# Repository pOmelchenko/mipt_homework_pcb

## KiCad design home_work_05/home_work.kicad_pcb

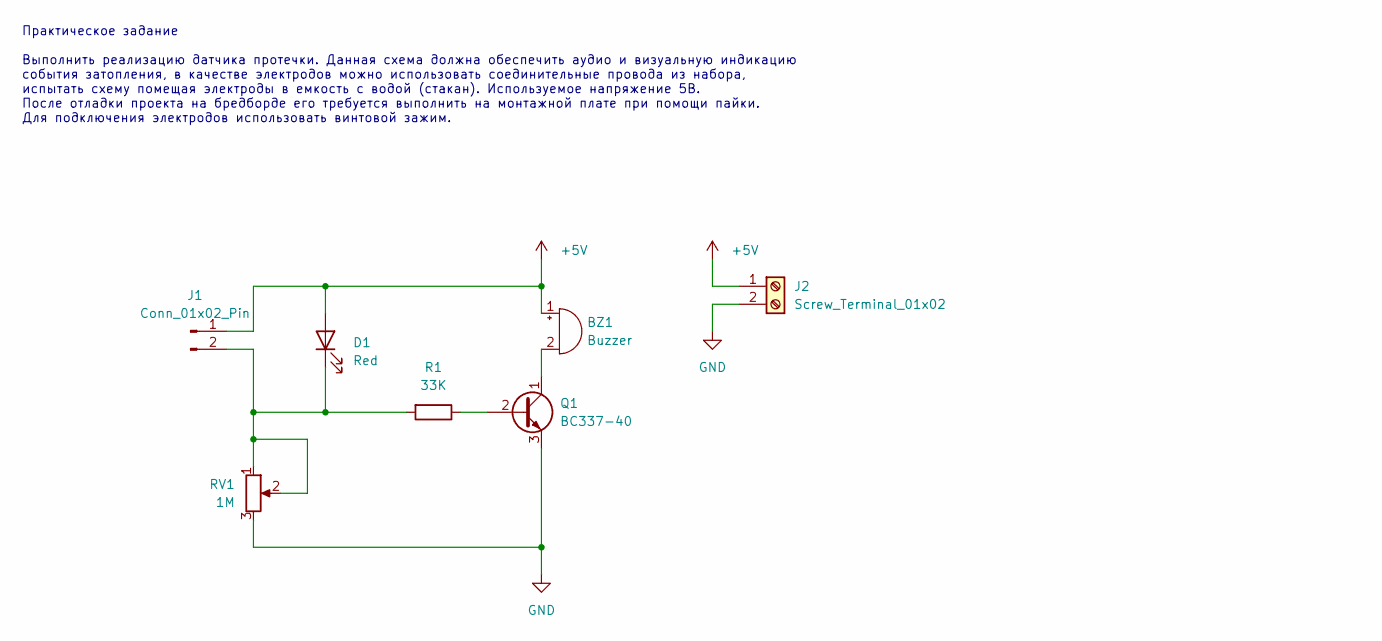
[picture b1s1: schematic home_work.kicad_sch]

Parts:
BZ1: Buzzer; Buzzer_15x7.5RM7.6
D1: Red; LED_D5.0mm
J1: Conn_01x02_Pin; JST_PH_B2B-PH-K_1x02_P2.00mm_Vertical
J2: Screw_Terminal_01x02; FK301-5.0
Q1: BC337-40; TO-92_Inline
R1: 33K; R_Axial_DIN0207_L6.3mm_D2.5mm_P10.16mm_Horizontal
RV1: 1M; Potentiometer_Bourns_3266Y_Vertical

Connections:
+5V: BZ1.1 (+), D1.2 (A), J1.1, J2.1
GND: J2.2, Q1.3 (E), RV1.3
unnamed: BZ1.2 (-), Q1.1 (C)
unnamed: D1.1 (K), J1.2, R1.2, RV1.1, RV1.2
unnamed: Q1.2 (B), R1.1

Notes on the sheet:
Практическое задание Выполнить реализацию датчика протечки. Данная схема должна обеспечить аудио и визуальную индикацию события затопления, в качестве электродов можно использовать соединительные провода из набора, испытать схему помещая электроды в емкость с водой (стакан). Используемое напряжение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

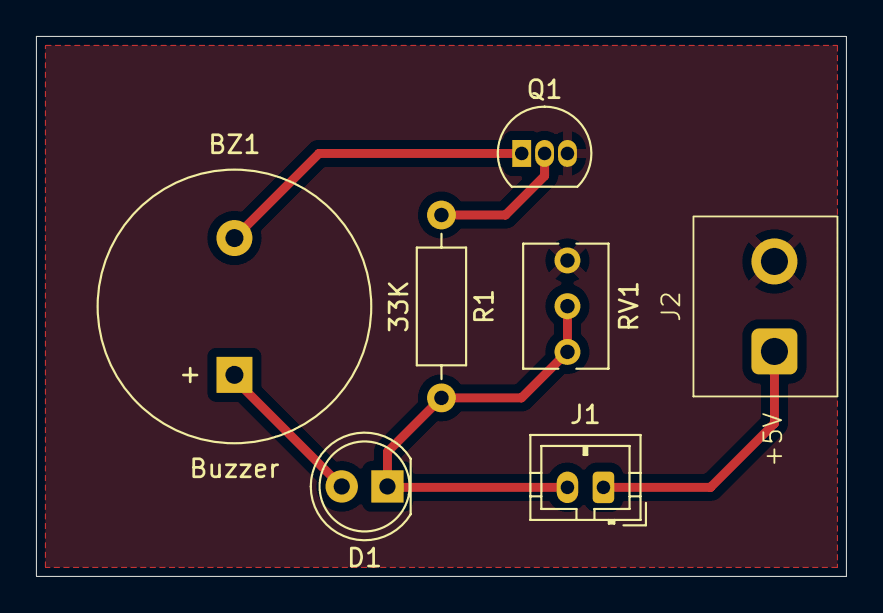
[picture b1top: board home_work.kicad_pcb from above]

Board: 2 copper layers, 45.0 x 30.0 mm, 7 parts (0 on the bottom side), 5 nets.

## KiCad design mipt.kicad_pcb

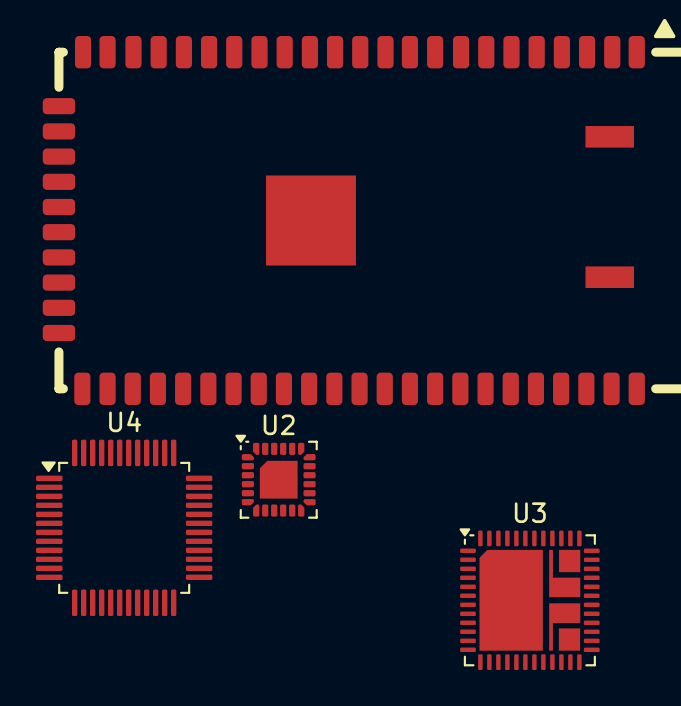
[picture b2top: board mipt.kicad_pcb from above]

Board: 2 copper layers, 4 parts (0 on the bottom side), 4 nets, no tracks yet.

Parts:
U1: HLK-7628N
U2: AW9523B; TQFN-24-1EP_4x4mm_P0.5mm_EP2.1x2.1mm
U3: XS2184; QFN-48-1EP_7x7mm_P0.5mm_EP5.6x5.6mm_1
U4: BL0910; LQFP-48_7x7mm_P0.5mm

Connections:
unnamed: U3.36 (DRAIN1), U3.39 (DRAIN1)
unnamed: U3.29 (DRAIN3), U3.30 (DRAIN3)
unnamed: U3.25 (DRAIN4), U3.26 (DRAIN4)
unnamed: U3.1 (N.C.), U3.15 (N.C.), U3.16 (N.C.), U3.17 (N.C.), U3.19 (N.C.), U3.20 (N.C.), U3.24 (N.C.), U3.38 (N.C.), U3.42 (N.C.), U3.43 (N.C.), U3.44 (N.C.), U3.46 (N.C.)

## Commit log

2024-06-28 init project
2024-07-03 started to do homework 2
2024-07-16 rename symbols library
2024-07-16 add english datasheet
2024-07-16 update symbol of AW9523B
2024-07-16 update basic schema
2024-07-16 add footprint for AW9523B
2024-07-16 update schemas
2024-07-17 update symbol
2024-07-17 add new symbols
2024-07-17 update symbols
2024-07-17 add fp table
2024-07-22 update HLK-7628N
2024-07-23 started to draw footprint for HLK-7628N
2024-07-23 update fp
2024-07-24 update BL0910
2024-07-24 some fixes
2024-07-27 updaye fp QFN-48-1EP
2024-07-28 fix some errors
2024-07-28 cleanup and reorganisation of project
2024-07-28 update schemas structure
2024-07-30 start home work 3. task 1
2024-07-30 fix led labesl to red
2024-08-03 home work 3
2024-08-05 home works 3 and 4
2024-08-06 fix schema for hw 4.1
2024-08-08 update path to hidden folder
2024-08-08 rename folder to hidden
2024-08-11 update hw2
2024-08-11 add datasheets
2024-08-11 update hw3
2024-08-11 add hw 4
2024-08-13 some fixes and add hw 5
2024-08-14 move old structure to temoprary folder
2024-08-14 add project for home work 2
2024-08-14 complete migration for home work 2
2024-08-14 complete migration for home work 3
2024-08-14 complete migration for home work 4
2024-08-14 complete migration for home work 5
2024-08-14 remove old datasheets
2024-08-16 fix home work 3
2024-08-16 do home work 5
2024-08-16 update pcb
2024-08-16 update pcb and footprint
2024-08-18 update home work 04
2024-08-18 update home work 05
2024-08-19 fix home work 04
2024-08-25 fix home work 03
